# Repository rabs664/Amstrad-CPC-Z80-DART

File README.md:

# Amstrad CPC Z80 DART
Simple Z80 DART board compatible with the Amstrad CPC and MX4 connector.

## Objective
Prototyping board to learn about the Z80 DART, and how to write Z80 assembly using an Amstrad CPC.

## Background
Part of a number of modular cards using Z80 associated peripherals and the Amstrad CPC.

See also;
[Amstrad CPC 2855 PIO](https://github.com/rabs664/Amstrad-CPC-8255-PIO)

## Backplane
[CPC Amstrad Expansion Backplane by revaldinho](https://github.com/revaldinho/cpc_ram_expansion/wiki/CPC-Expansion-Backplane)

## IO Addressing
The IO Address can be selected using two sets of jumpers (CS_HB and CS_LB), supporting the following base address.

* F8E0 and F8F0
* F9E0 and F9F0
* FAE0 and FAF0
* FBE0 and FBF0

See [CPC Wiki IO Port Summary](https://www.cpcwiki.eu/index.php/I/O_Port_Summary) for a list of known IO ports used on the Amstrad CPC.

## Testing
The Z80 DART board has been built and simple testing has been completed on an Amstrad CPC 6128.

Note testing was completed with a Z80 CTC board for the baud clock generation. The Amstrad Clock can be used as a baud clock but this will result in a non standard baud rate.

Note also an FTDI Serial Adapter was used to connect to a putty session.

IEI was tied high (via a 10K resistor) using a jumper to IEIE. 

## PCBs
PCBs are available from [Seeed Studio](https://www.seeedstudio.com/Simple-Z80-DART-board-compatible-with-the-Amstrad-CPC-and-MX4-connecto-g-1395237).

## Components
This [Digi-Key List](https://www.digikey.co.uk/en/mylists/list/F0CQ96V54G) contains all components excluding the Z80 DART and FTDI Serial Adapter.

Note the right angled header for the port connections was not available at the time of producing this list but all other components were in stock for shipping immediately.

## Assembler
[RASM](https://github.com/EdouardBERGE/rasm)

## Resources
[CPCWiki](https://www.cpcwiki.eu/index.php/Main_Page)

Z80 Application by James W Coffron ISBN 0-89588-094-6

## Acknowledgements
[@revaldinho](https://github.com/revaldinho)

Don Prefontaine 

Peter Murray

[@EdouardBERGE](https://github.com/EdouardBERGE)

# Release History
## Version 1.0
* First Release

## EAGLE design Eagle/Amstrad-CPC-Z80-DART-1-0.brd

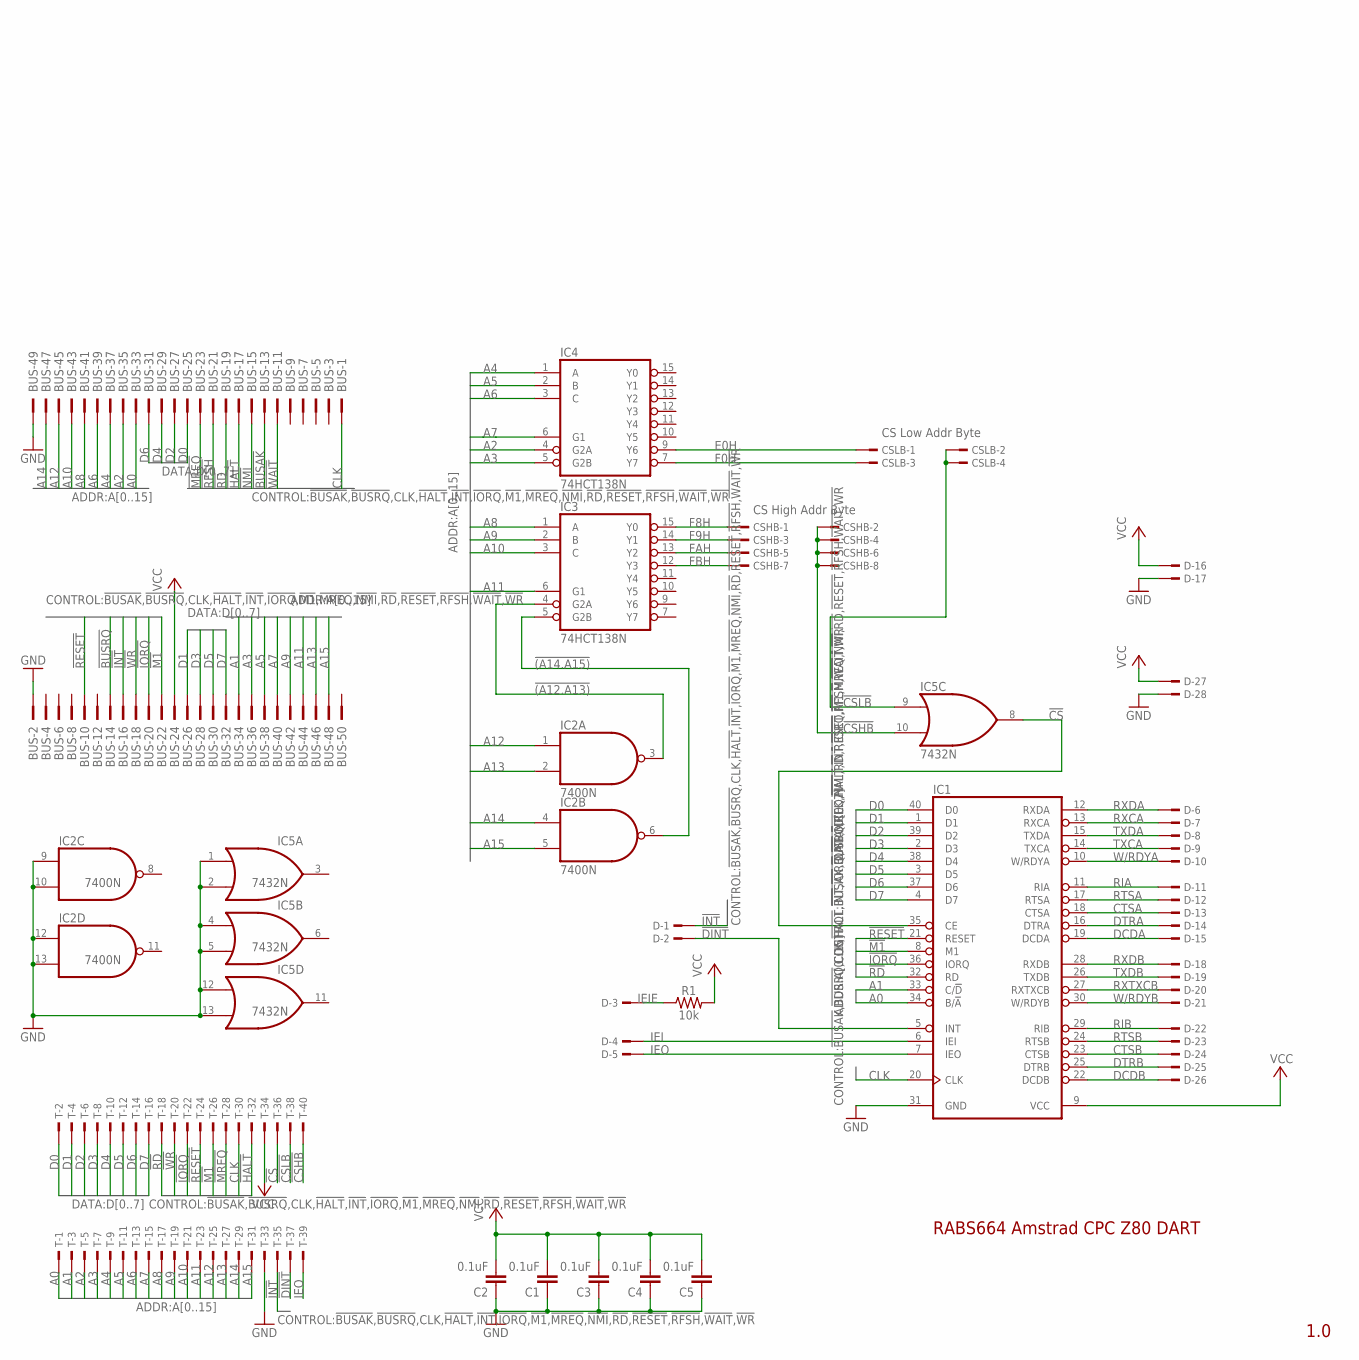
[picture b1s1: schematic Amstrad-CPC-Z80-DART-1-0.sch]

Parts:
BUS: 2550-; PAK100/2500-50
C1, C2, C3, C4, C5: 0.1uF; C050-025X075
CSHB: TSW-104-07-G-D; TSW-104-XX-G-D
CSLB: TSW-102-07-G-D; TSW-102-XX-G-D
D: TSW-128-07-G-S; TSW-128-XX-G-S
IC1: Z80DART; DIL40
IC2: 7400N; DIL14
IC3, IC4: 74HCT138N; DIL16
IC5: 7432N; DIL14
R1: 10k; AXIAL-0.3
T: TSW-120-07-G-D; TSW-120-XX-G-D

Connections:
!(A12.A13): IC2.3 (O), IC3.4 (G2A)
!(A14.A15): IC2.6 (O), IC3.5 (G2B)
!BUSAK: BUS.13
!BUSRQ: BUS.14
!CS: IC1.35 (CE), IC5.8 (O), T.36
!CSHB: CSHB.2, CSHB.4, CSHB.6, CSHB.8, IC5.10 (I1), T.40
!CSLB: CSLB.2, CSLB.4, IC5.9 (I0), T.38
!DINT: D.2, IC1.5 (INT), T.37
!HALT: BUS.17, T.32
!INT: BUS.16, D.1, T.35
!IORQ: BUS.20, IC1.36 (IORQ), T.22
!M1: BUS.22, IC1.8 (M1), T.26
!MREQ: BUS.23, T.28
!NMI: BUS.15
!RD: BUS.19, IC1.32 (RD), T.18
!RESET: BUS.10, IC1.21 (RESET), T.24
!RFSH: BUS.21
!WAIT: BUS.11
!WR: BUS.18, T.20
A0: BUS.33, IC1.34 (B/!A), T.1
A1: BUS.34, IC1.33 (C/!D), T.3
A2: BUS.35, IC4.4 (G2A), T.5
A3: BUS.36, IC4.5 (G2B), T.7
A4: BUS.37, IC4.1 (A), T.9
A5: BUS.38, IC4.2 (B), T.11
A6: BUS.39, IC4.3 (C), T.13
A7: BUS.40, IC4.6 (G1), T.15
A8: BUS.41, IC3.1 (A), T.17
A9: BUS.42, IC3.2 (B), T.19
A10: BUS.43, IC3.3 (C), T.21
A11: BUS.44, IC3.6 (G1), T.23
A12: BUS.45, IC2.1 (I0), T.25
A13: BUS.46, IC2.2 (I1), T.27
A14: BUS.47, IC2.4 (I0), T.29
A15: BUS.48, IC2.5 (I1), T.31
CLK: BUS.1, IC1.20 (CLK), T.30
CTSA: D.13, IC1.18 (CTSA)
CTSB: D.24, IC1.23 (CTSB)
D0: BUS.25, IC1.40 (D0), T.2
D1: BUS.26, IC1.1 (D1), T.4
D2: BUS.27, IC1.39 (D2), T.6
D3: BUS.28, IC1.2 (D3), T.8
D4: BUS.29, IC1.38 (D4), T.10
D5: BUS.30, IC1.3 (D5), T.12
D6: BUS.31, IC1.37 (D6), T.14
D7: BUS.32, IC1.4 (D7), T.16
DCDA: D.15, IC1.19 (DCDA)
DCDB: D.26, IC1.22 (DCDB)
DTRA: D.14, IC1.16 (DTRA)
DTRB: D.25, IC1.25 (DTRB)
E0H: CSLB.1, IC4.9 (Y6)
F0H: CSLB.3, IC4.7 (Y7)
F8H: CSHB.1, IC3.15 (Y0)
F9H: CSHB.3, IC3.14 (Y1)
FAH: CSHB.5, IC3.13 (Y2)
FBH: CSHB.7, IC3.12 (Y3)
GND: BUS.2, BUS.49, C1.1, C2.1, C3.1, C4.1, C5.1, D.17, D.28, IC1.31 (GND), IC2.7 (GND), IC2.9 (I0), IC2.10 (I1), IC2.12 (I0), IC2.13 (I1), IC3.8 (GND), IC4.8 (GND), IC5.1 (I0), IC5.2 (I1), IC5.4 (I0), IC5.5 (I1), IC5.7 (GND), IC5.12 (I0), IC5.13 (I1), T.33
IEI: D.4, IC1.6 (IEI)
IEIE: D.3, R1.P$1 (1)
IEO: D.5, IC1.7 (IEO), T.39
RIA: D.11, IC1.11 (RIA)
RIB: D.22, IC1.29 (RIB)
RTSA: D.12, IC1.17 (RTSA)
RTSB: D.23, IC1.24 (RTSB)
RXCA: D.7, IC1.13 (RXCA)
RXDA: D.6, IC1.12 (RXDA)
RXDB: D.18, IC1.28 (RXDB)
RXTXCB: D.20, IC1.27 (RXTXCB)
TXCA: D.9, IC1.14 (TXCA)
TXDA: D.8, IC1.15 (TXDA)
TXDB: D.19, IC1.26 (TXDB)
VCC: BUS.24, C1.2, C2.2, C3.2, C4.2, C5.2, D.16, D.27, IC1.9 (VCC), IC2.14 (VCC), IC3.16 (VCC), IC4.16 (VCC), IC5.14 (VCC), R1.P$2 (2), T.34
W/RDYA: D.10, IC1.10 (W/RDYA)
W/RDYB: D.21, IC1.30 (W/RDYB)

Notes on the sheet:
1.0
RABS664 Amstrad CPC Z80 DART
CS Low Addr Byte
CS High Addr Byte

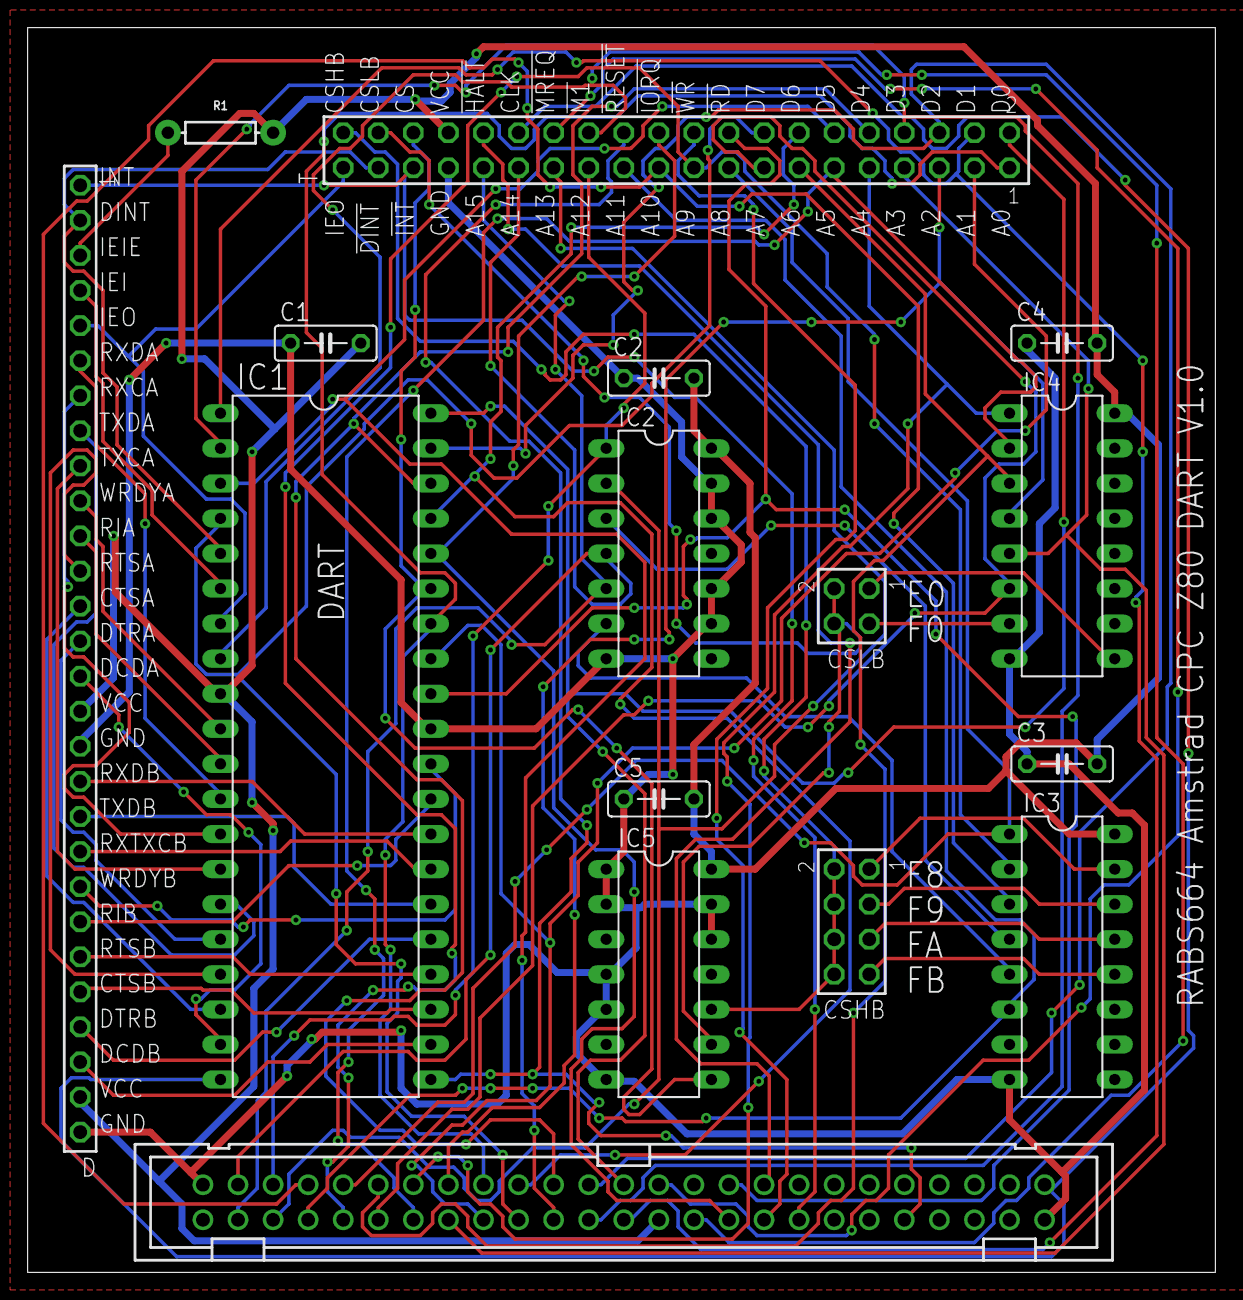
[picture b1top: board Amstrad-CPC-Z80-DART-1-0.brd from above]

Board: 2 copper layers, 86.0 x 90.2 mm, 16 parts (0 on the bottom side), 69 nets.

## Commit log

2023-07-09 Create LICENSE
2023-08-12 Update drttst02.asm
    Added FwTxtWrChar to print received characters on Amstrad CPC.
2023-08-12 Add files via upload
    Firmware library added for test 02.
2023-08-12 Update drttst02.asm
    Corrected last commit.
2023-08-25 Update README.md
    Added Seeed Studio reference for PCB.
2023-08-26 Update drtlib01.asm
    Corrected DRT_WR4_1_STOP_BIT was 0 should have been 1.
2025-07-20 Update README.md
    Remove Invalid URL links

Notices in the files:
parts and their libraries:
SparkFun-Resistors: Licensing: Creative Commons ShareAlike 4.0 International - https://creativecommons.org/licenses/by-sa/4.0
